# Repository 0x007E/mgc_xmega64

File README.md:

# `MGC_module` - ATxmega64

The `ATxmega64` (`mgc_module`) is an adaptable board for the [MeGARCard](https://github.com/0x007e/mgc). The board offers the possibility to control the `MeGARCard` with an [ATxmega64](#additional-information). The board itself is connected to the `MeGARCard` within the pcb-to-pcb connectors (no soldering necessary). With the onboard dip-switches the reset can be enabled/disabled for `PDI` programming.

> To mount the board on the `MeGARCard` disconnect the power source (`USB-C` connector) or any other used source from the MeGARCard!

| Experience  | Level                                                                               |
|:------------|:-----------------------------------------------------------------------------------:|
| Soldering   |  |

# Downloads

| Type      | File                                                                                                                                                              | Description     |
|:---------:|:-----------------------------------------------------------------------------------------------------------------------------------------------------------------:|:----------------|
| Schematic | [pdf](https://github.com/0x007E/mgc_xmega64/releases/latest/download/schematic.pdf) / [cadlab](https://cadlab.io/project/30510/main/files)                        | Schematic files |
| Board     | [pdf](https://github.com/0x007E/mgc_xmega64/releases/latest/download/pcb.pdf) / [cadlab](https://cadlab.io/project/30510/main/files)                              | Board file      |
| Drill     | [pdf](https://github.com/0x007E/mgc_xmega64/releases/latest/download/drill.pdf)                                                                                   | Drill file      |
| BoM | [xlsx](https://github.com/0x007E/mgc_xmega64/releases/latest/download/bom.xlsx) / [html](https://github.com/0x007E/mgc_xmega64/releases/latest/download/ibom.html)      | Bill of Material as Excel/interactive HTML |
| PCB    | [zip](https://github.com/0x007E/mgc_xmega64/releases/latest/download/kicad.zip) / [tar](https://github.com/0x007E/mgc_xmega64/releases/latest/download/kicad.tar.gz) | KiCAD/Gerber/BoM/Drill files       |

# Hardware

The pcb is created with `KiCAD`. All files are built with `github actions` so that they are ready for a production environment.

## PCB

The circuit board is populated on both sides (Top, Bottom). The best way for soldering the `SMD` components is within a vapor phase soldering system and for the `THT` components with a standard soldering system.

### Top Layer

### Bottom Layer

# Additional Information

| Type       | Link               | Description              |
|:----------:|:------------------:|:-------------------------|
| ATxmega64  | [pdf](https://ww1.microchip.com/downloads/en/DeviceDoc/ATxmega128-64-32-16A4U-DataSheet-DS40002166A.pdf) | ATxmega16/32/64/128 Data Sheet |

---

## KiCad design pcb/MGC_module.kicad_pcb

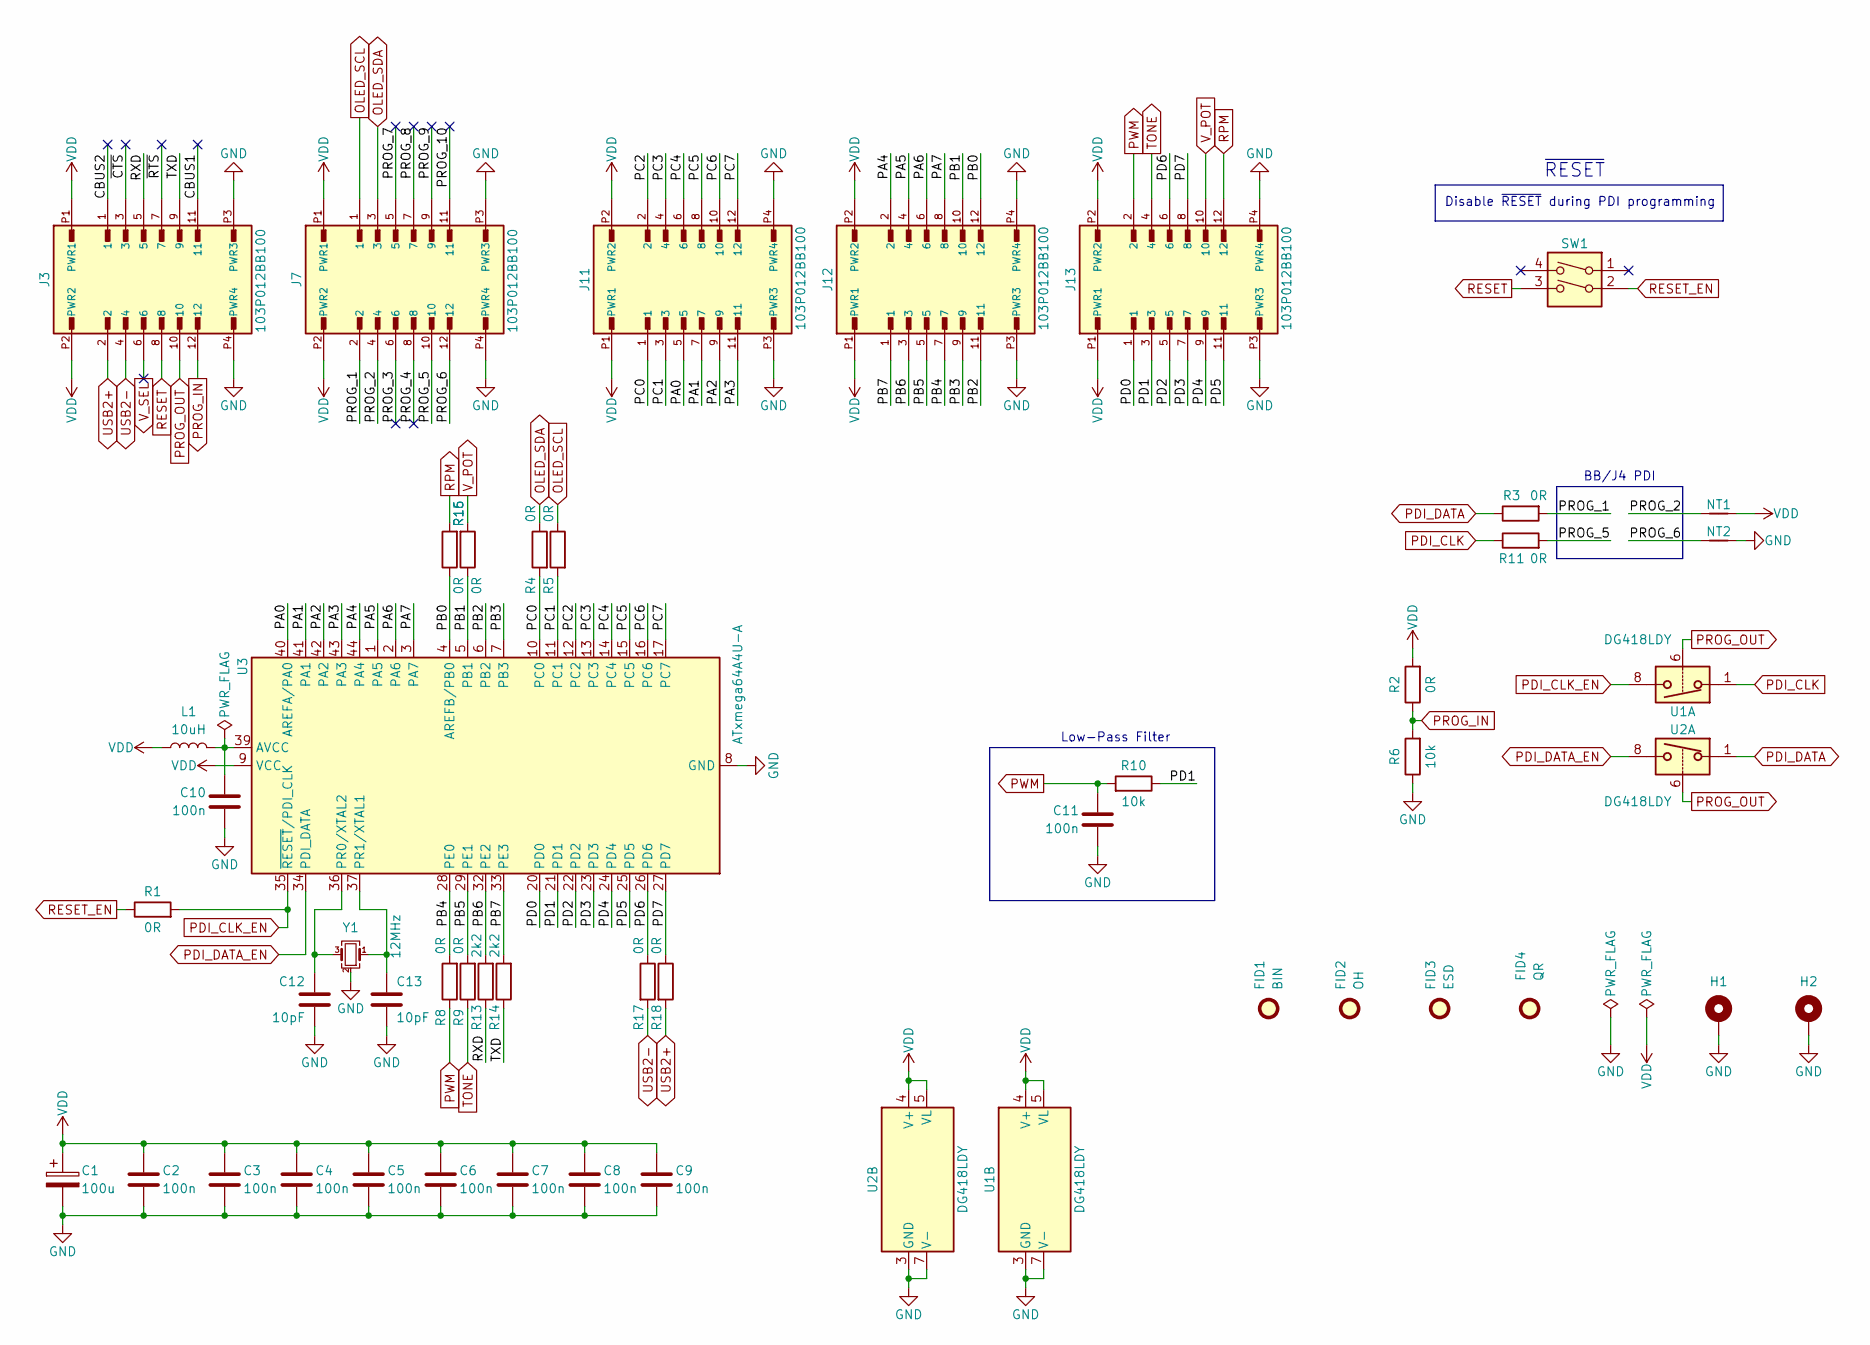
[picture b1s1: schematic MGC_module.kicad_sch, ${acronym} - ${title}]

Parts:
C1: 100u; CP_EIA-3528-21_Kemet-B; DigiKey 478-3877-1-ND
C2, C3, C4, C5, C6, C7, C8, C9, C10, C11: 100n; C_1206_3216Metric
C12, C13: 10pF; C_0603_1608Metric
FID1: BIN; WEEE-Logo_4.2x6mm_SilkScreen
FID2: OH; OSHW-Logo2_7.3x6mm_SilkScreen
FID3: ESD; ESD-Logo_6.6x6mm_SilkScreen
FID4: QR; QR_0x007e_very_small
H1, H2: MountingHole_Pad; MountingHole_2.7mm_M2.5_DIN965_Pad
J3, J7, J11, J12, J13: 103P012BB100; AMPHENOL_103P012BB100; DigiKey 609-103P012BB100CT-ND
L1: 10uH; L_1206_3216Metric
NT1, NT2: NetTie_2; NetTie-2_SMD_Pad0.5mm
R1, R2, R3, R4, R5, R8, R9, R11, R15, R16: 0R; R_1206_3216Metric
R6, R10: 10k; R_1206_3216Metric
R13, R14: 2k2; R_1206_3216Metric
R17, R18: 0R; R_0603_1608Metric; DigiKey CR0603AJ/-000EASCT-ND
SW1: SW_DIP_x02; SW_DIP_SPSTx02_Slide_6.7x6.64mm_W6.73mm_P2.54mm_LowProfile_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
U1, U2: DG418LDY; SOIC-8_3.9x4.9mm_P1.27mm; DigiKey DG417LEDY-T1-GE4CT-ND
U3: ATxmega64A4U-A; TQFP-44_10x10mm_P0.8mm; DigiKey ATXMEGA64A4U-AU-ND
Y1: 12MHz; Crystal_SMD_Abracon_ABM8AIG-4Pin_3.2x2.5mm

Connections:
/CBUS1: J3.11
/CBUS2: J3.1
/PA0: J11.5, U3.40 (AREFA/PA0)
/PA1: J11.7, U3.41 (PA1)
/PA2: J11.9, U3.42 (PA2)
/PA3: J11.11, U3.43 (PA3)
/PA4: J12.2, U3.44 (PA4)
/PA5: J12.4, U3.1 (PA5)
/PA6: J12.6, U3.2 (PA6)
/PA7: J12.8, U3.3 (PA7)
/PB0: J12.12, R15.1, U3.4 (AREFB/PB0)
/PB1: J12.10, R16.1, U3.5 (PB1)
/PB2: J12.11, U3.6 (PB2)
/PB3: J12.9, U3.7 (PB3)
/PB4: J12.7, R8.2, U3.28 (PE0)
/PB5: J12.5, R9.2, U3.29 (PE1)
/PB6: J12.3, R13.2, U3.32 (PE2)
/PB7: J12.1, R14.2, U3.33 (PE3)
/PC0: J11.1, R4.2, U3.10 (PC0)
/PC1: J11.3, R5.2, U3.11 (PC1)
/PC2: J11.2, U3.12 (PC2)
/PC3: J11.4, U3.13 (PC3)
/PC4: J11.6, U3.14 (PC4)
/PC5: J11.8, U3.15 (PC5)
/PC6: J11.10, U3.16 (PC6)
/PC7: J11.12, U3.17 (PC7)
/PD0: J13.1, U3.20 (PD0)
/PD1: J13.3, R10.1, U3.21 (PD1)
/PD2: J13.5, U3.22 (PD2)
/PD3: J13.7, U3.23 (PD3)
/PD4: J13.9, U3.24 (PD4)
/PD5: J13.11, U3.25 (PD5)
/PD6: J13.6, R17.1, U3.26 (PD6)
/PD7: J13.8, R18.1, U3.27 (PD7)
/PROG_1: J7.2, R3.2
/PROG_2: J7.4, NT1.1
/PROG_3: J7.6
/PROG_4: J7.8
/PROG_5: J7.10, R11.2
/PROG_6: J7.12, NT2.1
/PROG_7: J7.5
/PROG_8: J7.7
/PROG_9: J7.9
/PROG_10: J7.11
/RXD: J3.5, R13.1
/TXD: J3.9, R14.1
/~CTS: J3.3
/~RTS: J3.7
GND: C1.2, C2.2, C3.2, C4.2, C5.2, C6.2, C7.2, C8.2, C9.2, C10.2, C11.2, C12.2, C13.2, H1.1, H2.1, J3.P3 (PWR3), J3.P4 (PWR4), J7.P3 (PWR3), J7.P4 (PWR4), J11.P3 (PWR3), J11.P4 (PWR4), J12.P3 (PWR3), J12.P4 (PWR4), J13.P3 (PWR3), J13.P4 (PWR4), NT2.2, R6.1, U1.3 (GND), U1.7 (V-), U2.3 (GND), U2.7 (V-), U3.8 (GND), U3.18 (GND), U3.30 (GND), U3.38 (GND), Y1.2 (G), Y1.4 (G)
unnamed: C10.1, L1.2, U3.39 (AVCC)
unnamed: C12.1, U3.36 (PR0/XTAL2), Y1.3
unnamed: C13.1, U3.37 (PR1/XTAL1), Y1.1
OLED_SCL: J7.1, R5.1
OLED_SDA: J7.3, R4.1
PDI_CLK: R11.1, U1.1
PDI_CLK_EN: R1.2, U1.8, U3.35 (~RESET/PDI_CLK)
PDI_DATA: R3.1, U2.1
PDI_DATA_EN: U2.8, U3.34 (PDI_DATA)
PROG_IN: J3.12, R2.1, R6.2
PROG_OUT: J3.10, U1.6, U2.6
PWM: C11.1, J13.2, R8.1, R10.2
RESET: J3.8, SW1.3
RESET_EN: R1.1, SW1.2
RPM: J13.12, R15.2
TONE: J13.4, R9.1
USB2+: J3.2, R18.2
USB2-: J3.4, R17.2
VDD: C1.1, C2.1, C3.1, C4.1, C5.1, C6.1, C7.1, C8.1, C9.1, J3.P1 (PWR1), J3.P2 (PWR2), J7.P1 (PWR1), J7.P2 (PWR2), J11.P1 (PWR1), J11.P2 (PWR2), J12.P1 (PWR1), J12.P2 (PWR2), J13.P1 (PWR1), J13.P2 (PWR2), L1.1, NT1.2, R2.2, U1.4 (V+), U1.5 (VL), U2.4 (V+), U2.5 (VL), U3.9 (VCC), U3.19 (VCC), U3.31 (VCC)
V_POT: J13.10, R16.2
V_SEL: J3.6

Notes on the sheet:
Disable ~{RESET} during PDI programming
Low-Pass Filter
BB/J4 PDI
~{RESET}

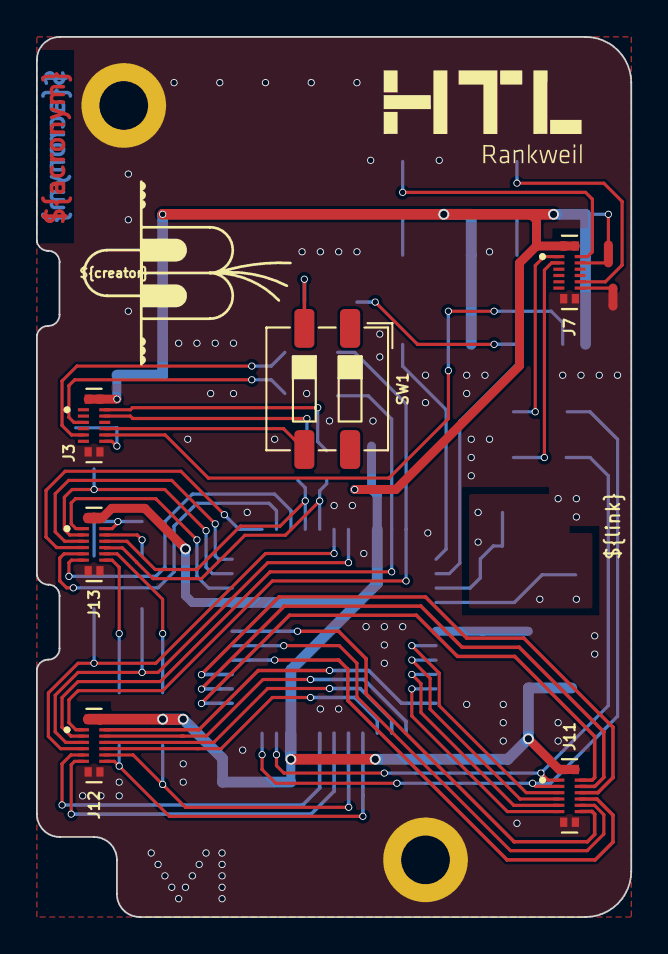
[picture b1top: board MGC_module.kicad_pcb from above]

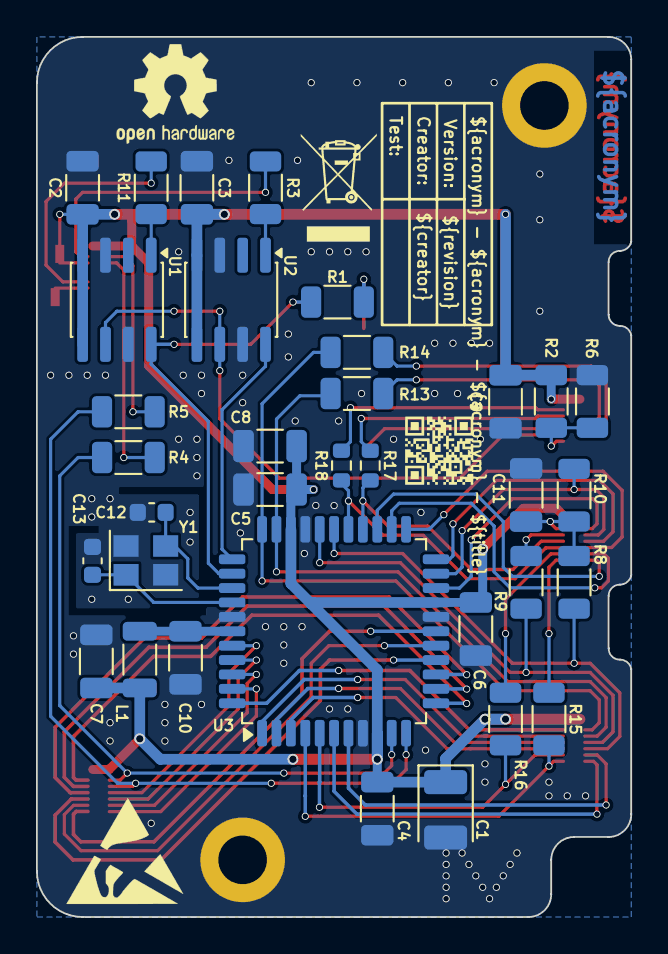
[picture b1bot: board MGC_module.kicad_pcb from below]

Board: 2 copper layers, 33.0 x 48.9 mm, 48 parts (38 on the bottom side), 59 nets.

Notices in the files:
README.md:
License CC By-NC-SA
parts and their libraries:
license: CC BY-NC-SA 4.0
